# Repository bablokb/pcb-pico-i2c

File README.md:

# pcb-pico-i2c
An I2C-connector shim for the Raspberrry Pi Pico

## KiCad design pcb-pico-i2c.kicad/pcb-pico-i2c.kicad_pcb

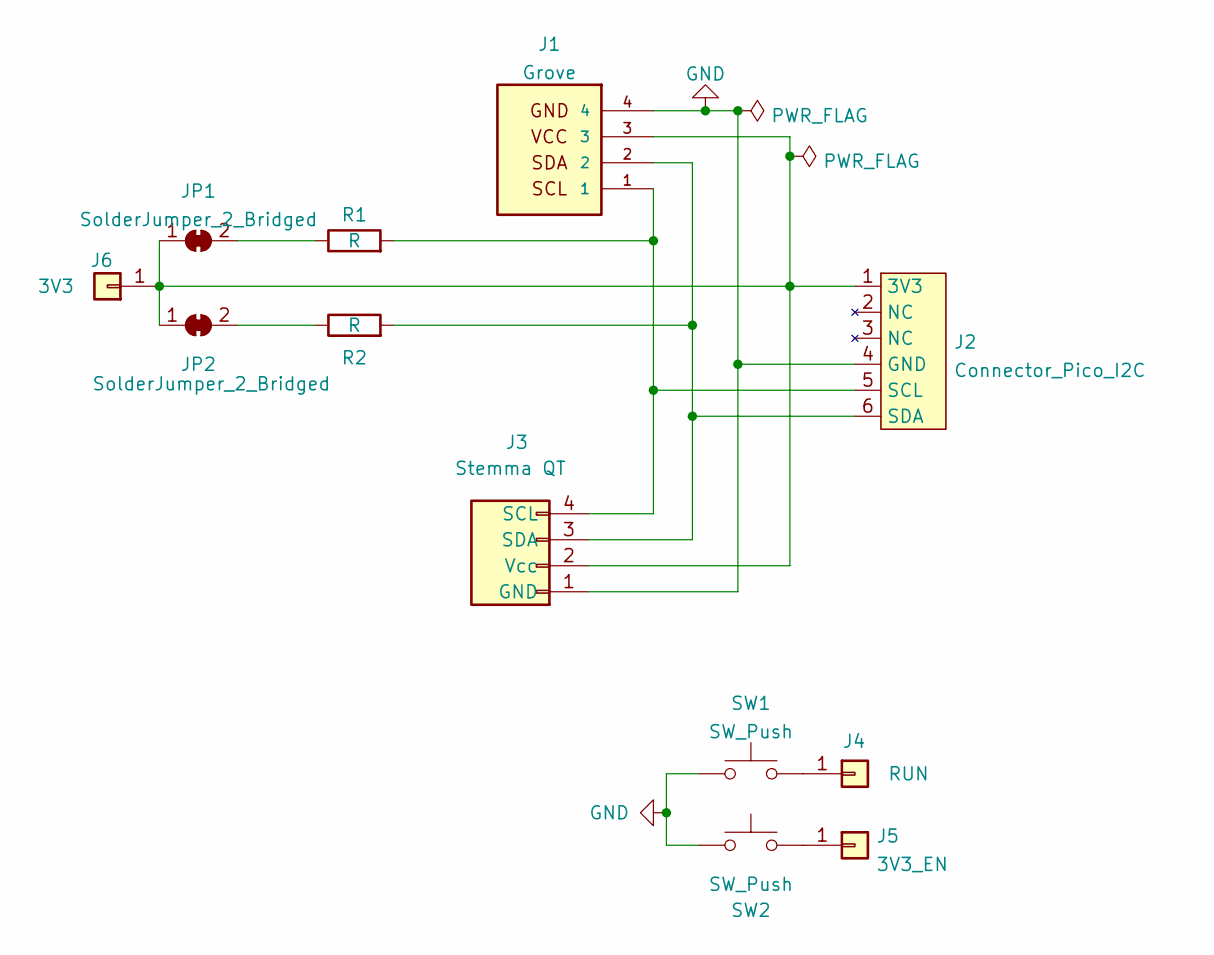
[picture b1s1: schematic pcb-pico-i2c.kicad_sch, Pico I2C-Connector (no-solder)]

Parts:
J1: Grove; grove_horizontal
J2: Connector_Pico_I2C; Connector_Pico-I2C
J3: Stemma QT; JST_SH_SM04B-SRSS-TB_1x04-1MP_P1.00mm_Horizontal
J4: RUN; PinHole_1x01
J5: 3V3_EN; PinHole_1x01
J6: 3V3; PinHole_1x01
JP1, JP2: SolderJumper_2_Bridged; SolderJumper-2_P1.3mm_Bridged_Pad1.0x1.5mm
R1, R2: R; R_0402_1005Metric; LCSC C25900
SW1: SW_Push; SW_PUSH_SLIM_1x4
SW2: SW_Push; SolderWire-0.1sqmm_1x02_P3.6mm_D0.4mm_OD1mm

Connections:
GND: J1.4, J2.4 (GND), J3.1 (GND), SW1.1, SW2.1
unnamed: J1.1, J2.5 (SCL), J3.4 (SCL), R1.2
unnamed: J1.2, J2.6 (SDA), J3.3 (SDA), R2.2
unnamed: J1.3, J2.1 (3V3), J3.2 (Vcc), J6.1, JP1.1 (A), JP2.1 (A)
unnamed: J4.1, SW1.2
unnamed: J5.1, SW2.2
unnamed: JP1.2 (B), R1.1
unnamed: JP2.2 (B), R2.1

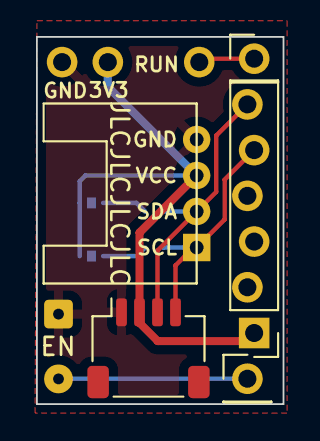
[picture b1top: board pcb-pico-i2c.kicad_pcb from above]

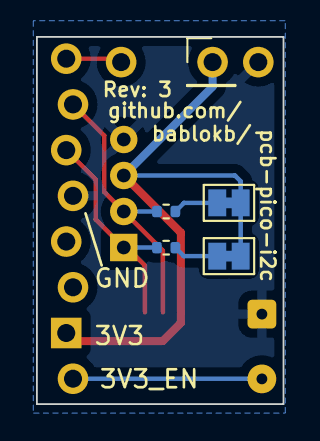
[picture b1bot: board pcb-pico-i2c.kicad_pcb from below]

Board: 2 copper layers, 13.7 x 20.4 mm, 12 parts (6 on the bottom side), 8 nets.

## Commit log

2022-07-15 added directory jlcpcb
2022-07-30 changes for Rev3 of board
